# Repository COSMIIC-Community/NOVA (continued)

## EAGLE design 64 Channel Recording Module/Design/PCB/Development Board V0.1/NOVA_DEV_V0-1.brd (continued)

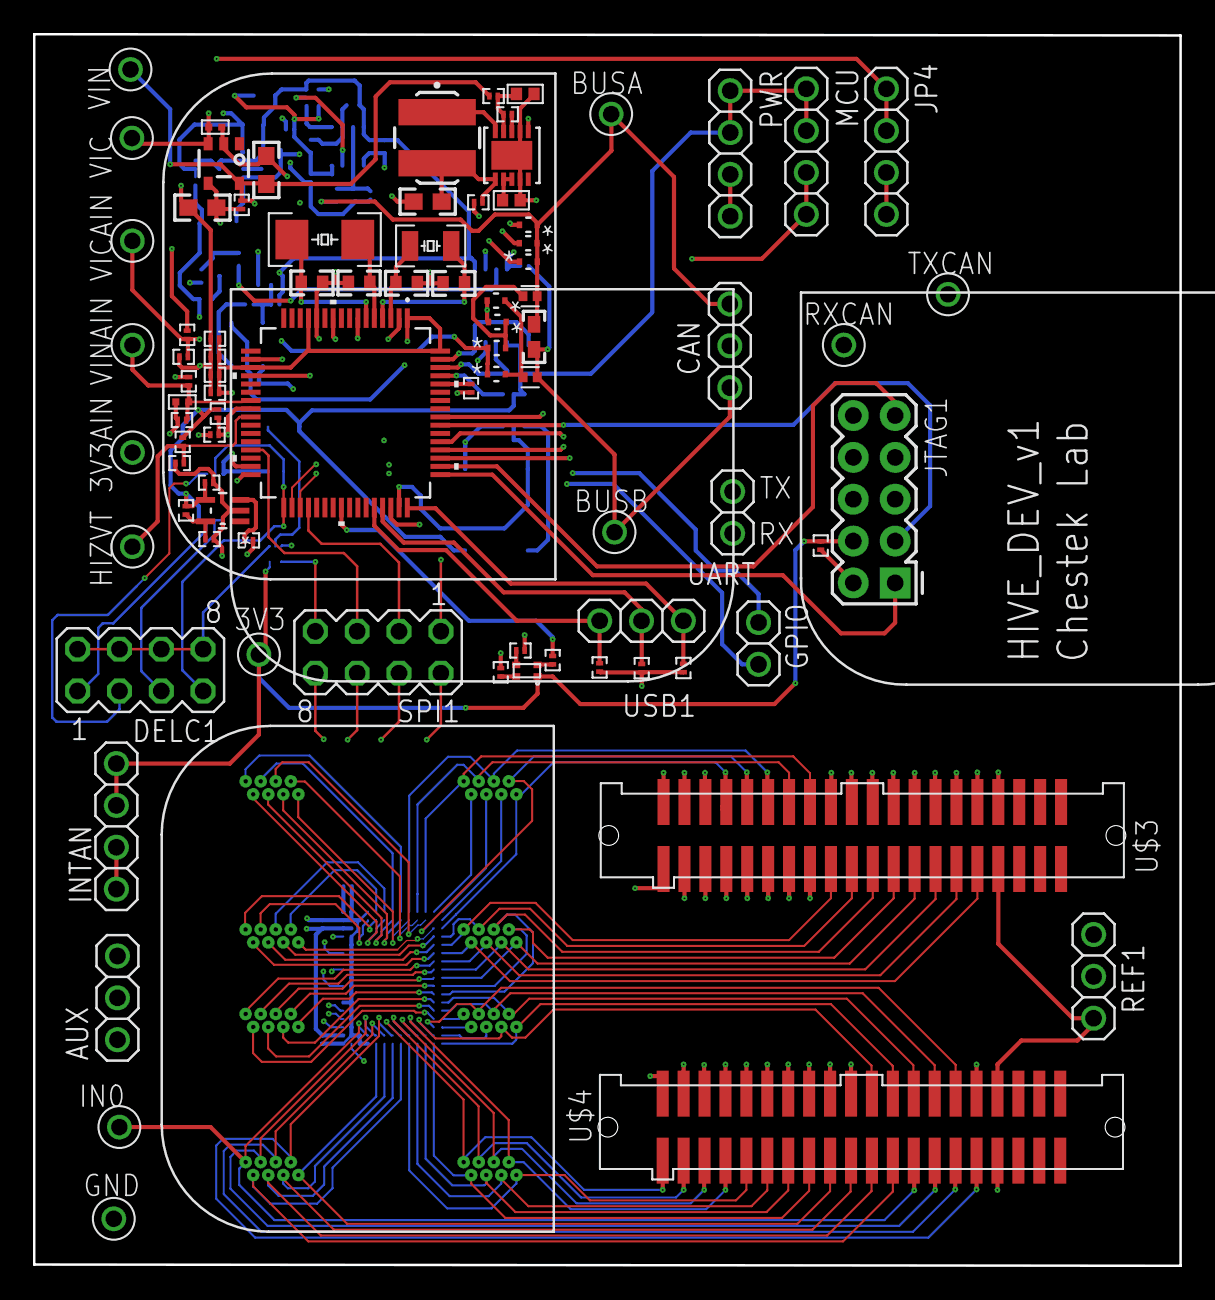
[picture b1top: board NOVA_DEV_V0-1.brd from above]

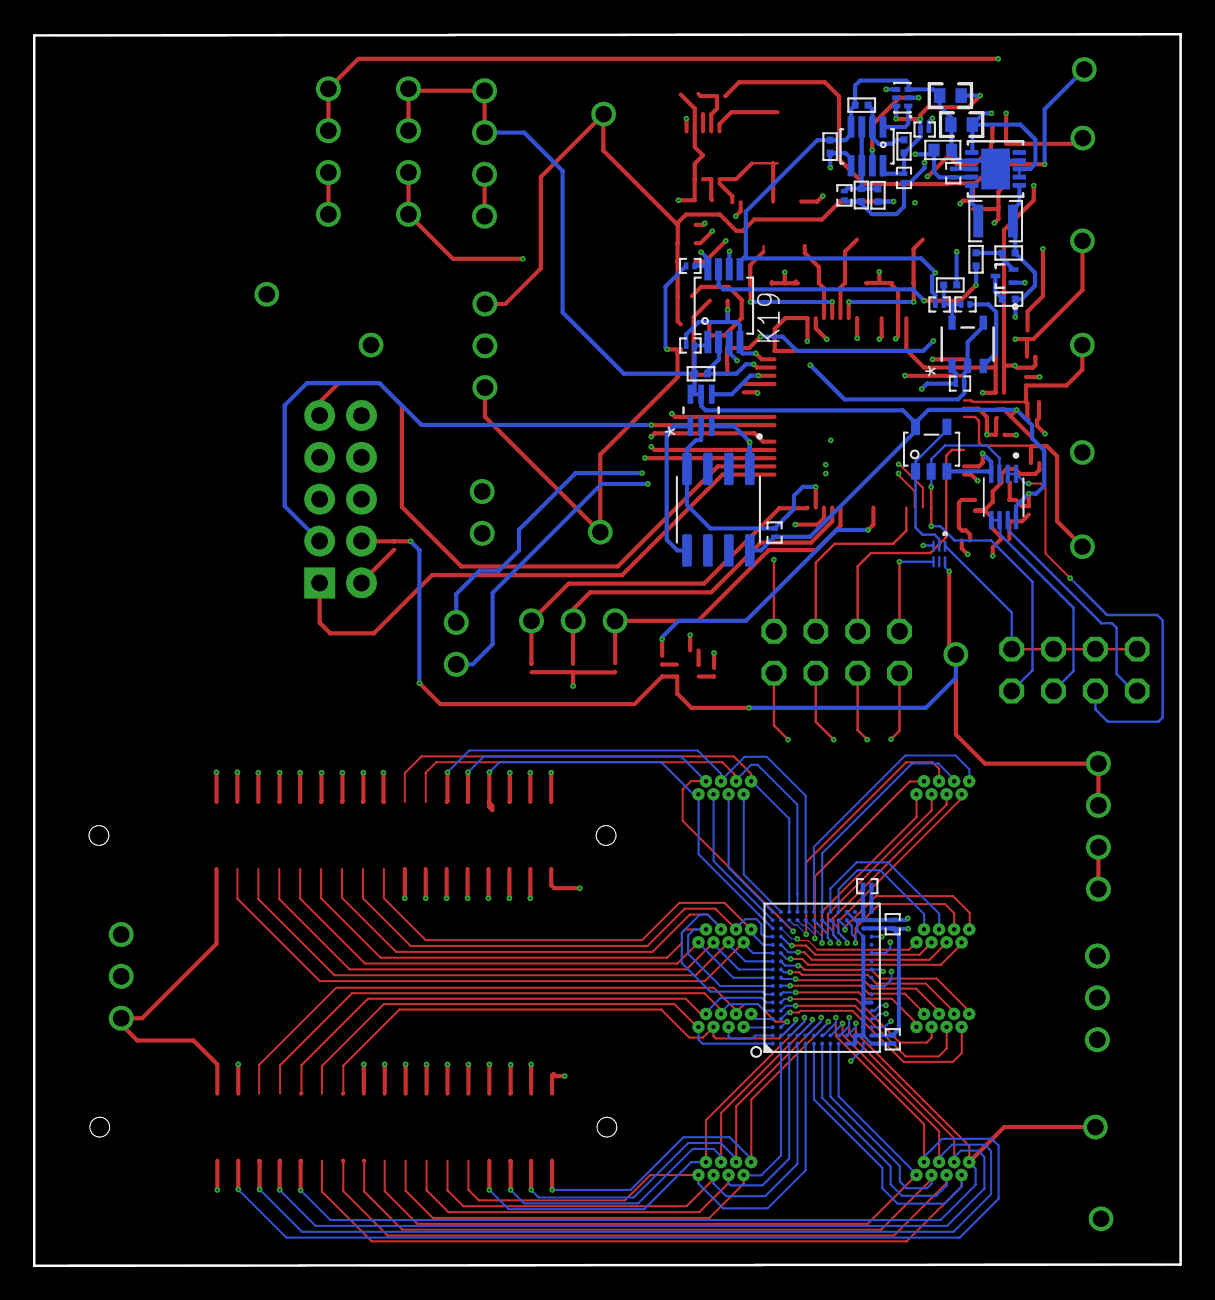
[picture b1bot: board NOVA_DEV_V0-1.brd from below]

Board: 4 copper layers, 69.6 x 74.8 mm, 125 parts (40 on the bottom side), 155 nets.
